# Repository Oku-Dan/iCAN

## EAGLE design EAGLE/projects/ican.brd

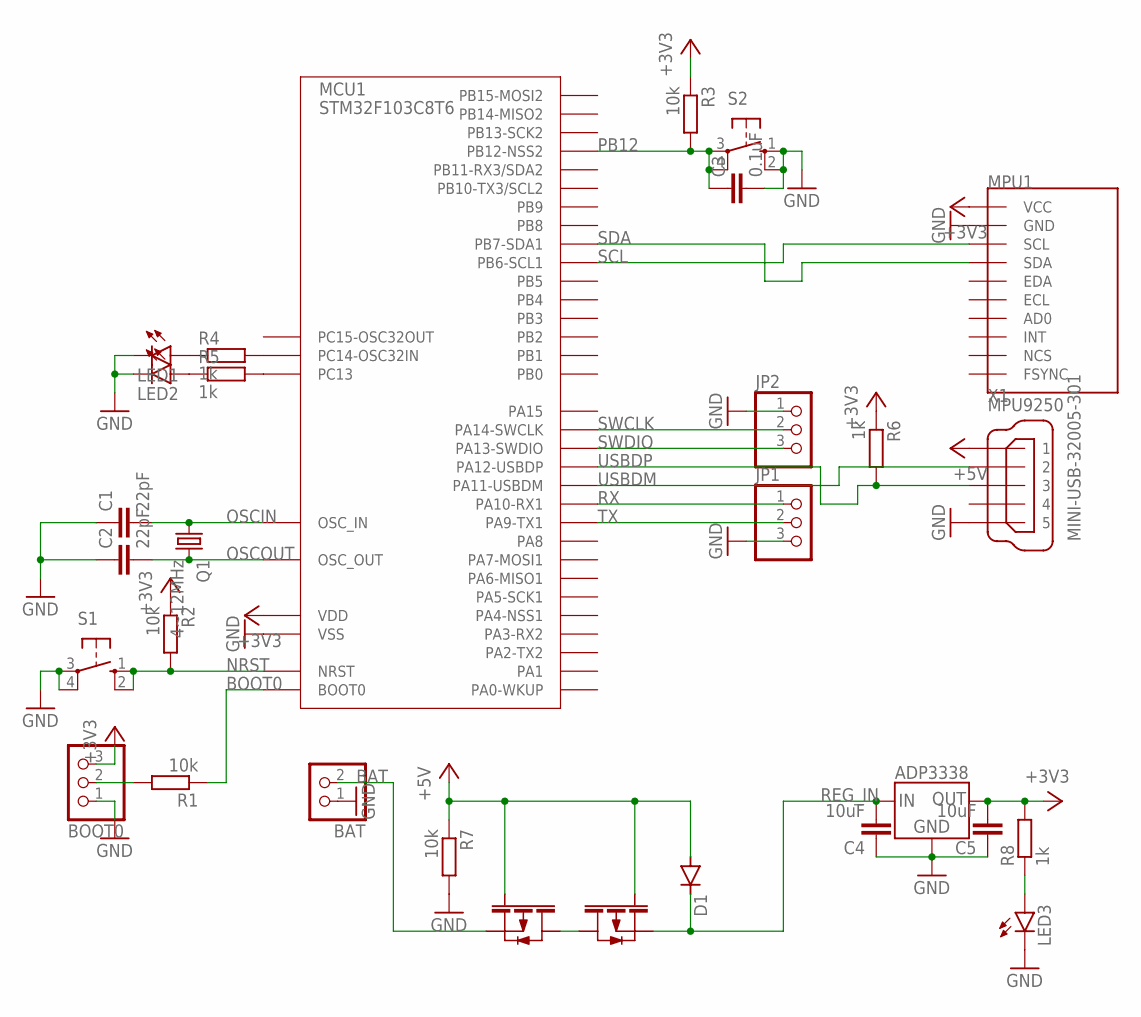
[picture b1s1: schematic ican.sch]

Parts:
BAT: PINHD-1X2; 1X02
BOOT0: PINHD-1X3; 1X03
C1, C2: 22pF; C2012
C3: 0.1uF; C2012
C4, C5: 10uF; C2012
D1: DIODE-SOD123; SOD123
FET1, FET2: PCH; SOT-23
IC1: ADP3338-3.3; SOT-223
JP1, JP2: PINHD-1X3; 1X03
LED1, LED2, LED3: LEDCHIPLED_1206; CHIPLED_1206
MCU1: STM32F103C8T6; LQFP48
MPU1: MPU9250; GY-9250
Q1: 4~12MHz; HC49/S
R1, R2, R3, R7: 10k; R2012
R4, R5, R6, R8: 1k; R2012
S1, S2: 10-XX; B3F-10XX
X1: MINI-USB-32005-301; 32005-301

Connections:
+3V3: BOOT0.3, C5.2, IC1.1 (OUT), IC1.2 (OUT), MCU1.1 (VDD), MCU1.9 (VDD), MCU1.24 (VDD), MCU1.36 (VDD), MCU1.48 (VDD), MPU1.P1 (VCC), R2.1, R3.1, R6.1, R8.2
+5V: D1.A, FET1.P$1, FET2.P$1, R7.1, X1.1
BAT: BAT.2, FET1.P$2
BOOT0: MCU1.44 (BOOT0), R1.1
BOOT0_: BOOT0.2, R1.2
GND: BAT.1, BOOT0.1, C1.1, C2.1, C3.2, C4.1, C5.1, IC1.4 (GND), JP1.3, JP2.1, LED1.C, LED2.C, LED3.C, MCU1.8 (VSS), MCU1.23 (VSS), MCU1.35 (VSS), MCU1.47 (VSS), MPU1.P2 (GND), R7.2, S1.3, S1.4 (P1), S2.1 (S), S2.2 (S1), X1.5
unnamed: MCU1.3 (PC14-OSC32IN), R4.2
unnamed: MCU1.2 (PC13), R5.2
unnamed: LED1.A, R4.1
unnamed: LED2.A, R5.1
unnamed: FET1.P$3, FET2.P$3
unnamed: LED3.A, R8.1
NRST: MCU1.7 (NRST), R2.2, S1.1 (S), S1.2 (S1)
OSCIN: C1.2, MCU1.5 (OSC_IN), Q1.1
OSCOUT: C2.2, MCU1.6 (OSC_OUT), Q1.2
PB12: C3.1, MCU1.25 (PB12-NSS2), R3.2, S2.3, S2.4 (P1)
REG_IN: C4.2, D1.C, FET2.P$2, IC1.3 (IN)
RX: JP1.1, MCU1.31 (PA10-RX1)
SCL: MCU1.42 (PB6-SCL1), MPU1.P3 (SCL)
SDA: MCU1.43 (PB7-SDA1), MPU1.P4 (SDA)
SWCLK: JP2.2, MCU1.37 (PA14-SWCLK)
SWDIO: JP2.3, MCU1.34 (PA13-SWDIO)
TX: JP1.2, MCU1.30 (PA9-TX1)
USBDM: MCU1.32 (PA11-USBDM), X1.2
USBDP: MCU1.33 (PA12-USBDP), R6.2, X1.3

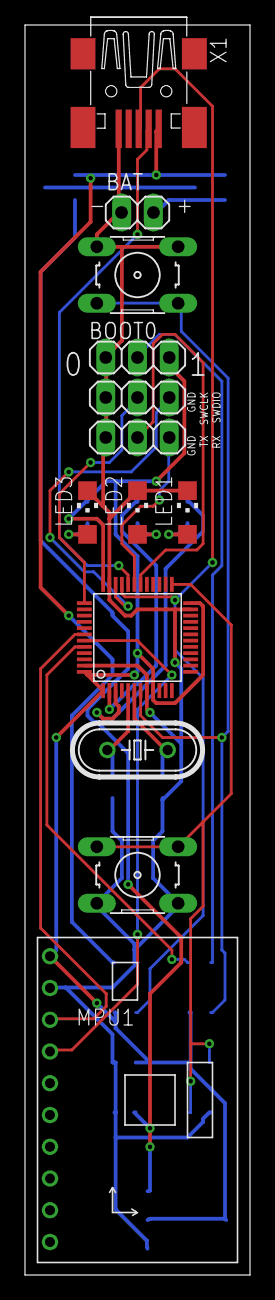
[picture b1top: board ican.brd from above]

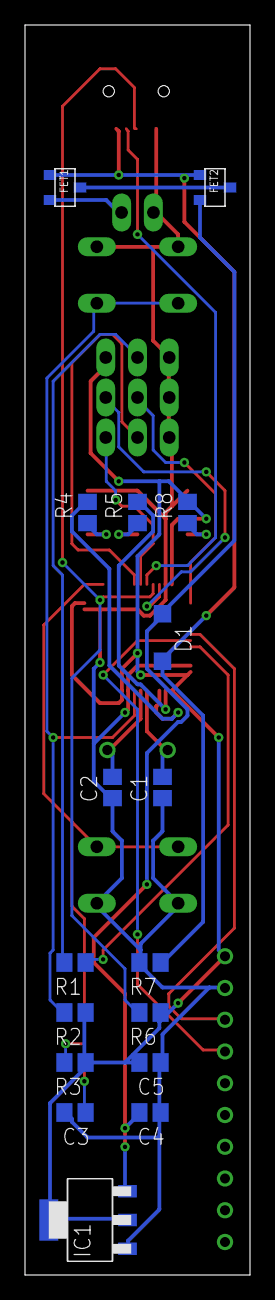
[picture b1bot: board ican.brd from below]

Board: 2 copper layers, 18.0 x 100.0 mm, 30 parts (17 on the bottom side), 25 nets.

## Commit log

2020-04-18 EAGLEのデータを追加
2020-04-18 Arduinoソースコードを追加
2020-04-18 学習用pythonソースを追加
